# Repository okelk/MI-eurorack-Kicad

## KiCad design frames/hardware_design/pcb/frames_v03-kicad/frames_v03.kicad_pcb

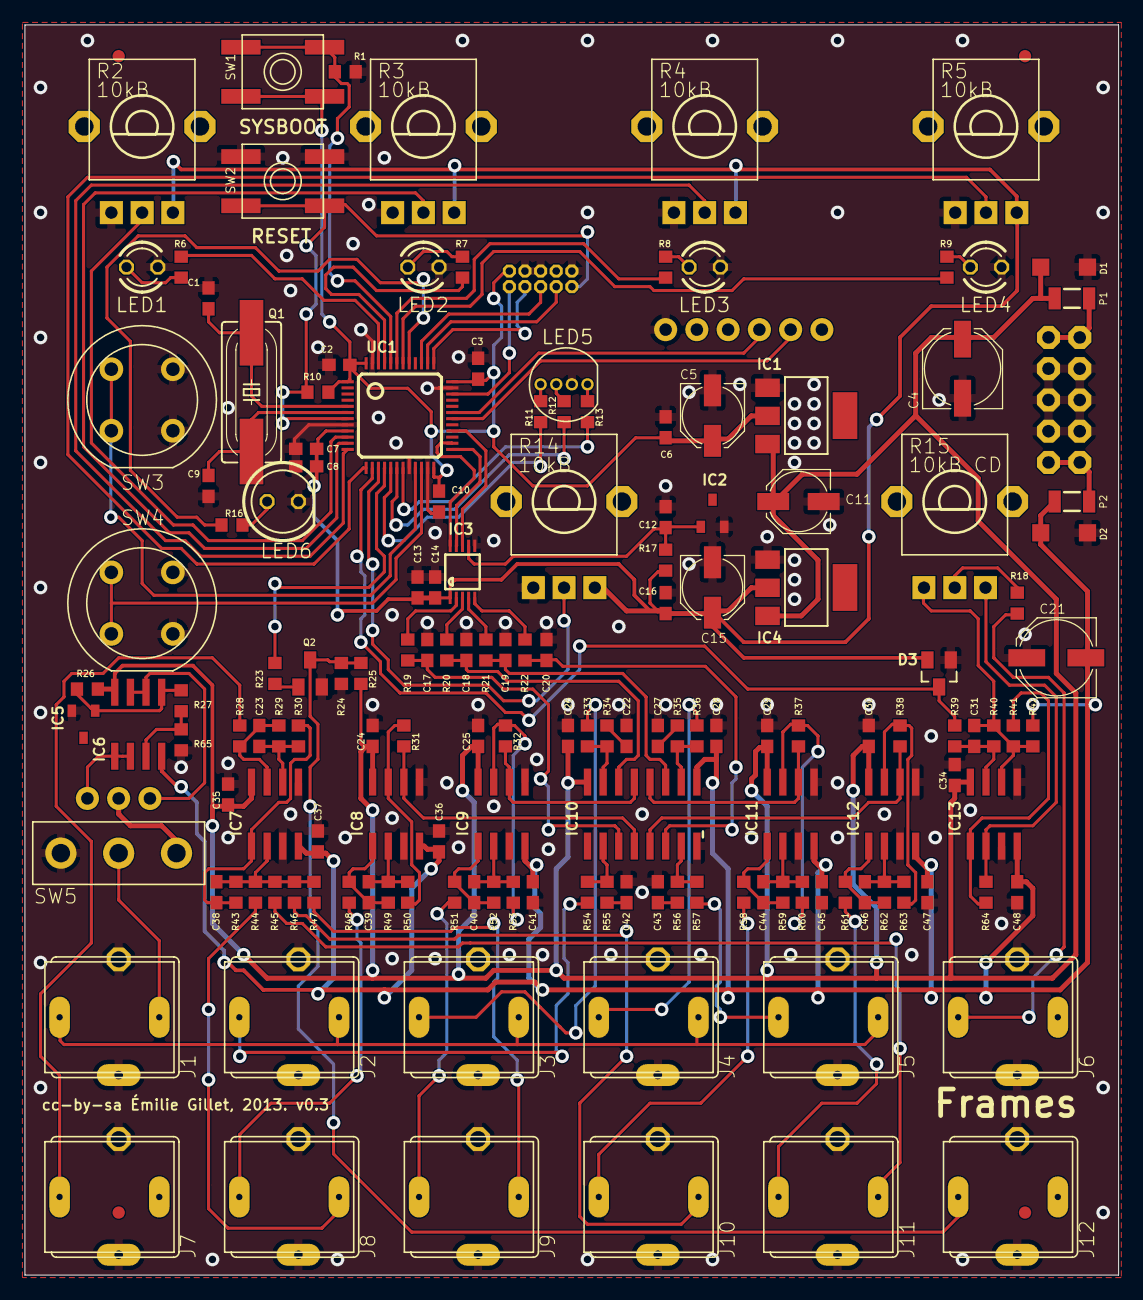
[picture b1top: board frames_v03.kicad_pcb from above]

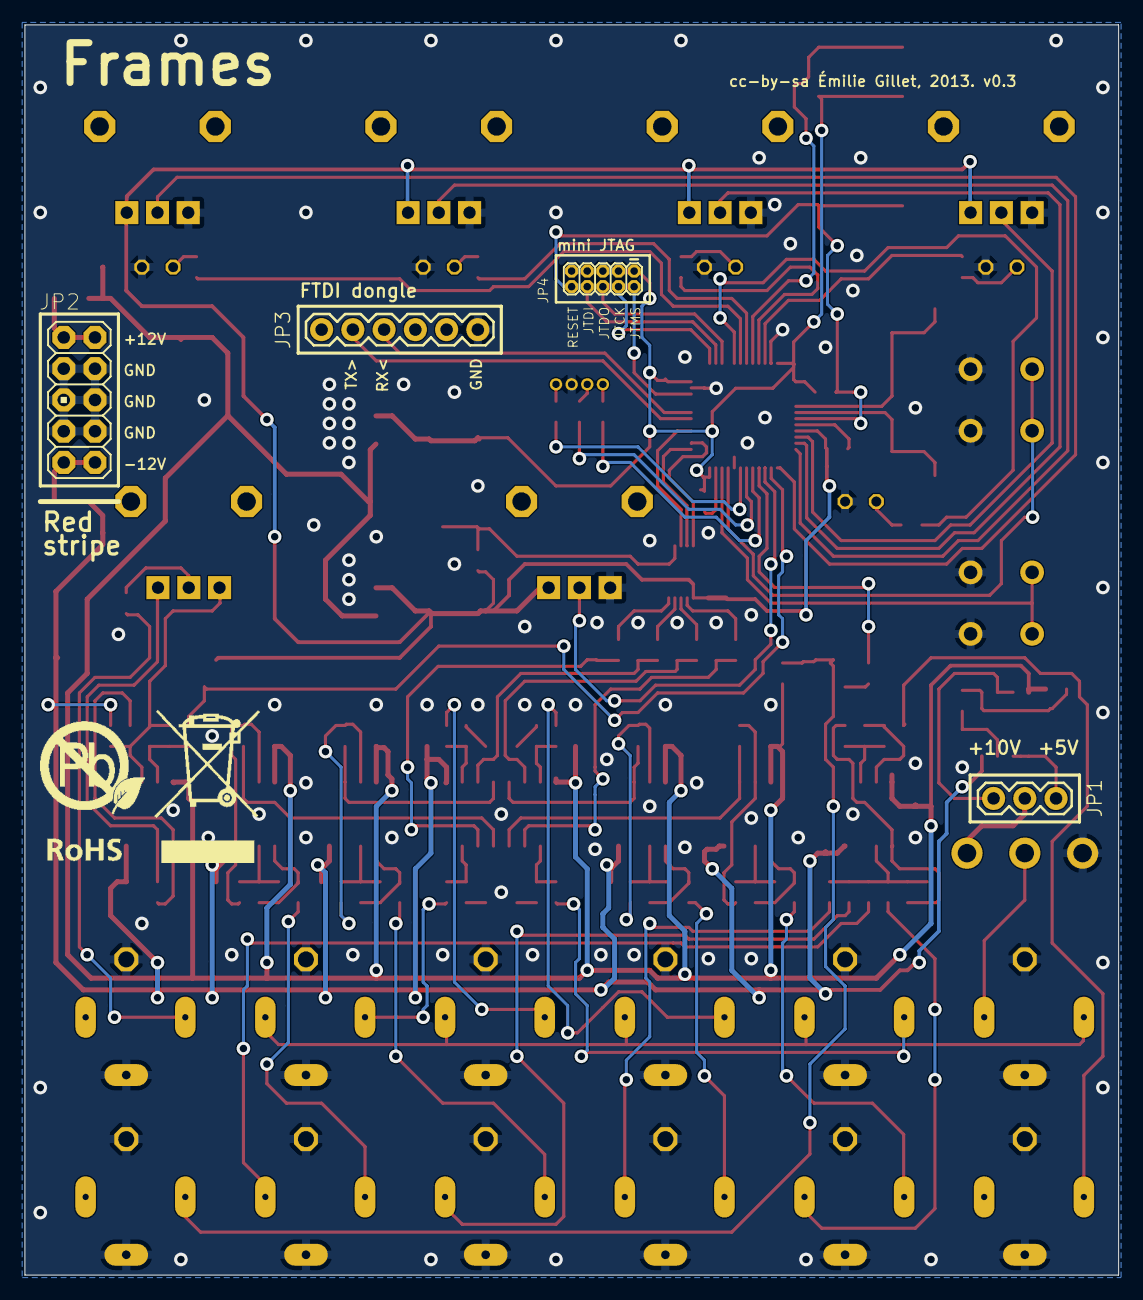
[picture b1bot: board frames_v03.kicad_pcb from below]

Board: 2 copper layers, 88.9 x 101.6 mm, 165 parts (5 on the bottom side), 110 nets.

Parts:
C1, C9, C23, C38, C39, C40, C44, C46: 18p; C0603
C2, C3, C6, C7, C10, C13, C16, C24, C25, C26, C28, C29, C30, C34, C35, C36, C37, C41, C45, C47, C48: 100n; C0603
C4, C21: 47u; PANASONIC_D
C5, C11, C15: 22u; PANASONIC_C
C8, C14: 3.3u; C0603
C12: 470n; C0603
C17, C18, C19, C20: 1u; C0603
C22, C27, C31, C42, C43: 560p; C0603
D1, D2: 1N5819HW; SOD123
D3: BAT54S; SOT23
F1, F2, F3, F4: FIDUCIAL1X2; FIDUCIAL-1X2
IC1, IC4: LM1117-3.3; SOT223
IC2: LM4040B25; DBZ_R-PDSO-G3
IC3: DAC124S085CIMT; MSOP10
IC5: LM4040B10; DBZ_R-PDSO-G3
IC6, IC7, IC8, IC9, IC11, IC12, IC13: TL072D; SO08
IC10: V2164SZ; SOIC16N
J1, J2, J3, J4, J5, J6, J7, J8, J9, J10, J11, J12: PJ301WQP; WQP_PJ_301BM
JP1: 1X03
JP2: M05X2PTH; AVR_ICSP
JP3: 1X06
JP4: M05X2MINIJTAG; 2X5-1.27
LED1, LED2, LED3, LED4: WP710A10GD; LED3MM
LED5: WP154A4SUREQBFZG; LED-TRICOLOR-THROUGHHOLE
LED6: WP7113SGD; LED5MM
P1, P2: PTCSMD; PTC-1206
Q1: 8MHz; HC49UP
Q2: MMBT3904; SOT23-BEC
R1, R10, R23: 10k; R0603
R2, R3, R4, R5, R14: 10kB; ALPS_POT_VERTICAL_PS
R6, R7, R8, R9, R11, R12, R13, R16, R19, R20, R21, R22: 100; R0603
R15: 10kB CD; ALPS_POT_VERTICAL_PS
R17, R34, R35, R55, R56: 510; R0603
R18, R27, R29, R30, R31, R32, R33, R36, R37, R38, R41, R44, R45, R46, R47, R49, R50, R52, R53, R54, R57, R59, R60, R62, R63, R64, R65: 100k; R0603
R24: 3.3k; R0603
R25, R26: 4.7k; R0603
R28, R39, R48, R51, R58, R61: 1.0k; R0603
R40: 33k; R0603
R42: 240k; R0603
R43: 49.9k; R0603
SW1, SW2: EVQ-Q2
SW3, SW4: D6R
SW5: ES_100SP1T6B11M2QEH_SMALL
U$1: EURORACK_TEMPLATE
U$3: ROHS_BIG
UC1: STM32F103CBT6; LQFP48

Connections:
+3V3: C2.1, C3.1, C5.+, C6.1, C10.1, IC1.2, JP4.1, R10.2, SW1.B, SW1.B', UC1.1, UC1.24, UC1.36, UC1.48
+3V3_A: C7.1, C8.1, C13.1, C14.1, C15.+, C16.1, D3.2, IC3.1, IC4.2, R2.P$1, R3.P$1, R4.P$1, R5.P$1, R14.P$1, R17.1, UC1.9
ADD_SWITCH: SW3.A1, SW3.A2, UC1.21
AREF_2.5: C12.1, IC2.1, IC3.7, R17.2
AREF_5: IC6.1, IC6.2, JP1.1
AREF_10: IC6.6, IC6.7, JP1.3
AREF_10_0: IC5.1, IC6.5, R26.2, R27.2
BOOT_FLASH: R1.2, SW1.A, SW1.A', UC1.44
DAC_MOSI: IC3.8, UC1.28
DAC_SCK: IC3.10, UC1.26
DAC_SS: IC3.9, UC1.25
DEL_SWITCH: SW4.A1, SW4.A2, UC1.22
FB_CURRENT: IC10.2, R54.2, R55.2
FB_CURRENT1: IC10.15, R33.2, R34.2
FB_CURRENT2: IC10.10, R35.2, R36.2
FB_CURRENT3: IC10.7, R56.2, R57.2
FRAME_CHANGE: R23.1, UC1.16
GAIN_1: C17.1, IC10.3, R19.2
GAIN_2: C18.1, IC10.14, R20.2
GAIN_3: C19.1, IC10.11, R21.2
GAIN_4: C20.1, IC10.6, R22.2
GATE2_LED: LED3.A, R8.2
GATE3_LED: LED2.A, R7.2
GATE4_LED: LED1.A, R6.2
GND: C1.1, C2.2, C3.2, C4.-, C5.-, C6.2, C7.2, C8.2, C9.1, C10.2, C11.-, C12.2, C13.2, C14.2, C15.-, C16.2, C17.2, C18.2, C19.2, C20.2, C21.+, C22.2, C24.2, C25.2, C26.2, C27.2, C28.1, C29.2, C30.2, C34.2, C35.2, C36.1, C37.1, C41.1, C42.2, C43.2, C45.1, C47.1, C48.1, D1.A, D2.C, D3.1, IC1.1, IC2.2, IC3.6, IC4.1, IC5.2, IC7.3, IC7.5, IC8.3, IC8.5, IC9.3, IC9.5, IC10.8, IC11.3, IC11.5, IC12.3, IC12.5, IC13.3, IC13.5, J1.GND, J1.GND2, J2.GND, J2.GND2, J3.GND, J3.GND2, J4.GND, J4.GND2, J5.GND, J5.GND2, J6.GND, J6.GND2, J7.GND, J7.GND2, J8.GND, J8.GND2, J9.GND, J9.GND2, J10.GND, J10.GND2, J11.GND, J11.GND2, J12.GND, J12.GND2, JP2.3, JP2.4, JP2.5, JP2.6, JP2.7, JP2.8, JP3.1, JP4.3, JP4.5, JP4.9, LED1.K, LED2.K, LED3.K, LED4.K, LED5.GND, LED6.K, Q2.E, R1.1, R2.P$3, R3.P$3, R4.P$3, R5.P$3, R14.P$3, R24.1, R65.1, SW2.A, SW2.A', SW3.B1, SW3.B2, SW4.B1, SW4.B2, SW5.O, UC1.8, UC1.20, UC1.23, UC1.35, UC1.47
IN_1: J2.TIP, R54.1
IN_2: J3.TIP, R33.1
IN_3: J4.TIP, R36.1
IN_4: J5.TIP, R57.1
JTCK: JP4.4, UC1.37
JTDI: JP4.8, UC1.38
JTDO: JP4.6, UC1.39
JTMS: JP4.2, UC1.34
LED_B: R12.1, UC1.18
LED_CH1: R6.1, UC1.46
LED_CH2: R7.1, UC1.45
LED_CH3: R8.1, UC1.43
LED_CH4: R9.1, UC1.42
LED_FRAME: R16.1, UC1.41
LED_G: R11.1, UC1.17
LED_R: R13.1, UC1.19
MODULATION: D3.3, R39.1, UC1.14
unnamed: IC13.2, R15.P$1, R64.2
unnamed: C42.1, R55.1
unnamed: J7.TIP, R28.2
unnamed: IC9.7, R32.2, R53.1
unnamed: R15.P$2, R18.2
unnamed: LED4.A, R9.2
unnamed: C1.2, Q1.2, UC1.5
unnamed: C9.2, Q1.1, UC1.6
unnamed: IC13.1, R41.2, R64.1
unnamed: C27.1, R35.1
unnamed: J6.TIP, R18.1
unnamed: IC8.6, IC10.4, R31.1
unnamed: C31.2, IC13.7, R39.2, R40.1
unnamed: C31.1, IC13.6, R15.P$3, R40.2, R41.1, R42.1
unnamed: C39.1, IC8.2, R49.1, R50.2
unnamed: C39.2, IC8.1, R48.1, R49.2
unnamed: C23.2, IC7.7, R28.1, R29.2
unnamed: C22.1, R34.1
unnamed: C38.1, IC7.2, R43.1, R44.2, R45.2, R46.2, R47.2
unnamed: IC9.6, IC10.13, R32.1
unnamed: C23.1, IC7.6, R29.1, R30.2
unnamed: C40.1, IC9.2, R52.1, R53.2
unnamed: C40.2, IC9.1, R51.1, R52.2
unnamed: IC10.12, IC11.6, R37.1
unnamed: LED6.A, R16.2
unnamed: C44.1, IC11.2, R59.1, R60.2
unnamed: C44.2, IC11.1, R58.1, R59.2
unnamed: C43.1, R56.1
unnamed: C38.2, IC7.1, R30.1, R43.2
unnamed: IC10.5, IC12.6, R38.1
unnamed: IC6.3, R27.1, R65.2
unnamed: C46.1, IC12.2, R62.1, R63.2
unnamed: C46.2, IC12.1, R61.1, R62.2
unnamed: J1.SW, SW5.P
unnamed: LED5.RED, R13.2
unnamed: LED5.BLU, R12.2
unnamed: LED5.GRN, R11.2
unnamed: IC3.2, R19.1
unnamed: J8.TIP, R48.2
unnamed: IC3.3, R20.1
unnamed: JP1.2, SW5.S
unnamed: IC3.4, R21.1
unnamed: J12.TIP, Q2.C, R24.2, R25.1
unnamed: IC3.5, R22.1
unnamed: Q2.B, R23.2
unnamed: IC12.7, R38.2, R63.1
unnamed: J9.TIP, R51.2
unnamed: J11.TIP, R61.2
unnamed: J10.TIP, R58.2
unnamed: JP2.1, JP2.2, P1.2
unnamed: JP2.9, JP2.10, P2.2
PAN: J1.TIP, J2.SW, J3.SW, J4.SW, J5.SW
POT_CH1: R2.P$2, UC1.10
POT_CH2: R3.P$2, UC1.11
POT_CH3: R4.P$2, UC1.12
POT_CH4: R5.P$2, UC1.13
POT_FRAME: R14.P$2, UC1.15
RESET: JP4.10, R10.1, SW2.B, SW2.B', UC1.7
RX: JP3.4, UC1.31
TX: JP3.5, UC1.30
VCA0_1: IC8.7, R31.2, R50.1
VCA0_3: IC11.7, R37.2, R60.1
VCA_1: J8.SW, R44.1
VCA_2: J9.SW, R47.1
VCA_3: J10.SW, R46.1
VCA_4: J11.SW, R45.1
VCC: C4.+, C11.+, C24.1, C25.1, C26.1, C29.1, C30.1, C34.1, C35.1, D1.C, IC1.3, IC4.3, IC6.8, IC7.8, IC8.8, IC9.8, IC10.16, IC11.8, IC12.8, IC13.8, P1.1, R25.2, R26.1
VEE: C21.-, C28.2, C36.2, C37.2, C41.2, C45.2, C47.2, C48.2, D2.A, IC6.4, IC7.4, IC8.4, IC9.4, IC10.9, IC11.4, IC12.4, IC13.4, P2.1, R42.2

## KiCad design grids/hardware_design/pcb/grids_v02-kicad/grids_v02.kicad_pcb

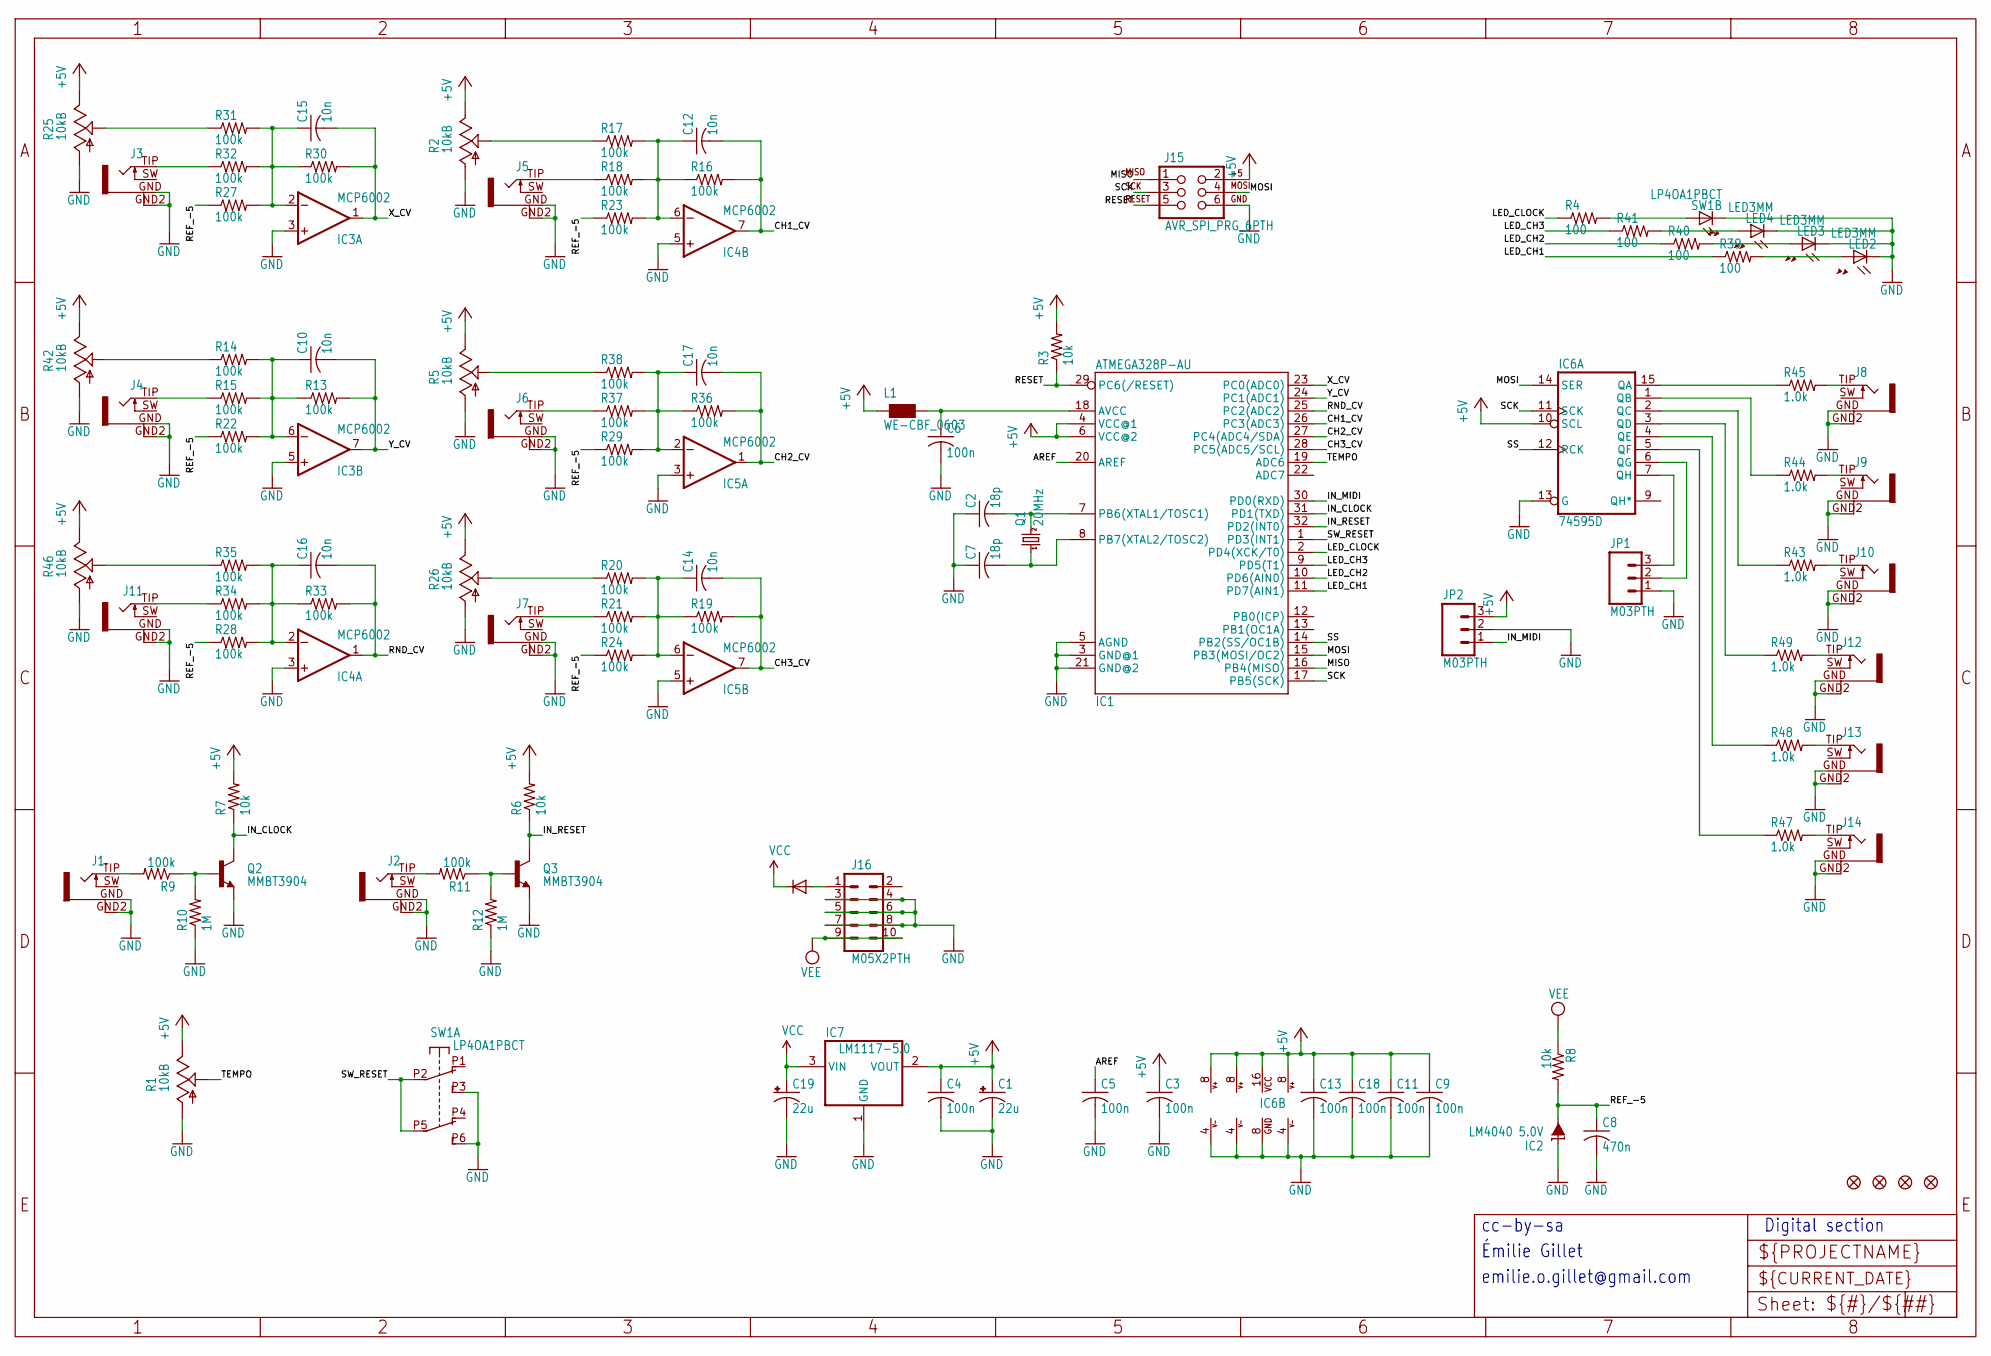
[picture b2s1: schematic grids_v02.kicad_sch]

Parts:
C1, C19: 22u; PANASONIC_C
C2, C7: 18p; C0603
C3, C4, C5, C6, C9, C11, C13, C18: 100n; C0603
C8: 470n; C0603
C10, C12, C14, C15, C16, C17: 10n; C0603
D1: 1N5819HW; SOD123
F1, F2, F3, F4: FIDUCIAL1X2; FIDUCIAL-1X2
IC1: ATMEGA328P-AU; TQFP32-08
IC2: LM4040 5.0V; DBZ_R-PDSO-G3
IC3, IC4, IC5: MCP6002; SO08
IC6: 74595D; SO16
IC7: LM1117-5.0; SOT223
J1, J2, J3, J4, J5, J6, J7, J8, J9, J10, J11, J12, J13, J14: PJ301WQP; WQP_PJ_301BM
J15: AVR_SPI_PRG_6PTH; 2X3
J16: M05X2PTH; AVR_ICSP
JP1, JP2: M03PTH; 1X03
L1: WE-CBF_0603; 0603
LED2, LED3, LED4: LED3MM
Q1: 20MHz; HC49UP
Q2, Q3: MMBT3904; SOT23-BEC
R1, R2, R5, R25, R26, R46: 10kB; ALPS_POT_VERTICAL_PS
R3, R6, R7, R8: 10k; R0603
R4, R39, R40, R41: 100; R0603
R9, R11, R13, R14, R15, R16, R17, R18, R19, R20, R21, R22, R23, R24, R27, R28, R29, R30, R31, R32, R33, R34, R35, R36, R37, R38: 100k; R0603
R10, R12: 1M; R0603
R42: 10kB; ALPS_POT_VERTICAL_PS4
R43, R44, R45, R47, R48, R49: 1.0k; R0603
SW1: LP4OA1PBCT

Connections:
+5V: C1.+, C3.1, C4.1, C9.1, C11.1, C13.1, C18.1, IC1.4 (VCC@1), IC1.6 (VCC@2), IC3.8 (V+), IC4.8 (V+), IC5.8 (V+), IC6.10 (SCL), IC6.16 (VCC), IC7.2 (VOUT), J15.2, JP2.3, L1.1, R1.P$1 (E), R2.P$1 (E), R3.2, R5.P$1 (E), R6.2, R7.2, R25.P$1 (E), R26.P$1 (E), R42.P$1 (E), R46.P$1 (E)
AREF: C5.1, IC1.20 (AREF)
CH1_CV: C12.2, IC1.26 (PC3(ADC3)), IC4.7 (OUT), R16.2
CH2_CV: C17.2, IC1.27 (PC4(ADC4/SDA)), IC5.1 (OUT), R36.2
CH3_CV: C14.2, IC1.28 (PC5(ADC5/SCL)), IC5.7 (OUT), R19.2
CLOCK_OUT: IC6.6 (QG), JP1.2
GATE1_IN: J1.TIP (2), R9.2
GATE1_LED: R4.2, SW1.L1
GATE2_IN: J2.TIP (2), R11.2
GATE2_LED: LED4.A, R41.2
GATE3_LED: LED3.A, R40.2
GATE4_LED: LED2.A, R39.2
GND: C1.-, C2.1, C3.2, C4.2, C5.2, C6.2, C7.1, C8.2, C9.2, C11.2, C13.2, C18.2, C19.-, IC1.3 (GND@1), IC1.5 (AGND), IC1.21 (GND@2), IC2.1 (C), IC3.3 (+IN), IC3.4 (V-), IC3.5 (+IN), IC4.3 (+IN), IC4.4 (V-), IC4.5 (+IN), IC5.3 (+IN), IC5.4 (V-), IC5.5 (+IN), IC6.8 (GND), IC6.13 (G), IC7.1 (GND), J1.GND (1), J1.GND2 (4), J2.GND (1), J2.GND2 (4), J3.GND (1), J3.GND2 (4), J4.GND (1), J4.GND2 (4), J5.GND (1), J5.GND2 (4), J6.GND (1), J6.GND2 (4), J7.GND (1), J7.GND2 (4), J8.GND (1), J8.GND2 (4), J9.GND (1), J9.GND2 (4), J10.GND (1), J10.GND2 (4), J11.GND (1), J11.GND2 (4), J12.GND (1), J12.GND2 (4), J13.GND (1), J13.GND2 (4), J14.GND (1), J14.GND2 (4), J15.6, J16.3, J16.4, J16.5, J16.6, J16.7, J16.8, JP1.1, JP2.2, LED2.K (C), LED3.K (C), LED4.K (C), Q2.E, Q3.E, R1.P$3 (A), R2.P$3 (A), R5.P$3 (A), R10.1, R12.1, R25.P$3 (A), R26.P$3 (A), R42.P$3 (A), R46.P$3 (A), SW1.L2, SW1.P3 (A3), SW1.P6 (B3)
IN_CLOCK: IC1.31 (PD1(TXD)), Q2.C, R7.1
IN_MIDI: IC1.30 (PD0(RXD)), JP2.1
IN_RESET: IC1.32 (PD2(INT0)), Q3.C, R6.1
LED_CH1: IC1.11 (PD7(AIN1)), R39.1
LED_CH2: IC1.10 (PD6(AIN0)), R40.1
LED_CH3: IC1.9 (PD5(T1)), R41.1
LED_CLOCK: IC1.2 (PD4(XCK/T0)), R4.1
MISO: IC1.16 (PB4(MISO)), J15.1
MOSI: IC1.15 (PB3(MOSI/OC2)), IC6.14 (SER), J15.4
unnamed: Q2.B, R9.1, R10.2
unnamed: Q3.B, R11.1, R12.2
unnamed: D1.A, J16.1
unnamed: J14.TIP (2), R47.2
unnamed: J13.TIP (2), R48.2
unnamed: J12.TIP (2), R49.2
unnamed: R25.P$2 (S), R31.1
unnamed: J3.TIP (2), R32.1
unnamed: C10.1, IC3.6 (-IN), R13.1, R14.2, R15.2, R22.2
unnamed: R14.1, R42.P$2 (S)
unnamed: J4.TIP (2), R15.1
unnamed: C16.1, IC4.2 (-IN), R28.2, R33.1, R34.2, R35.2
unnamed: R35.1, R46.P$2 (S)
unnamed: J11.TIP (2), R34.1
unnamed: C12.1, IC4.6 (-IN), R16.1, R17.2, R18.2, R23.2
unnamed: R2.P$2 (S), R17.1
unnamed: J5.TIP (2), R18.1
unnamed: C17.1, IC5.2 (-IN), R29.2, R36.1, R37.2, R38.2
unnamed: R5.P$2 (S), R38.1
unnamed: J6.TIP (2), R37.1
unnamed: C14.1, IC5.6 (-IN), R19.1, R20.2, R21.2, R24.2
unnamed: R20.1, R26.P$2 (S)
unnamed: J7.TIP (2), R21.1
unnamed: IC6.15 (QA), R45.1
unnamed: IC6.1 (QB), R44.1
unnamed: C15.1, IC3.2 (-IN), R27.2, R30.1, R31.2, R32.2
unnamed: IC6.2 (QC), R43.1
unnamed: IC6.3 (QD), R49.1
unnamed: IC6.4 (QE), R48.1
unnamed: IC6.5 (QF), R47.1
unnamed: J8.TIP (2), R45.2
unnamed: J9.TIP (2), R44.2
unnamed: J10.TIP (2), R43.2
unnamed: C6.1, IC1.18 (AVCC), L1.2
unnamed: C7.2, IC1.8 (PB7(XTAL2/TOSC2)), Q1.1
unnamed: C2.2, IC1.7 (PB6(XTAL1/TOSC1)), Q1.2
RANDOM_GATE: IC6.7 (QH), JP1.3
REF_-5: C8.1, IC2.2 (A), R8.2, R22.1, R23.1, R24.1, R27.1, R28.1, R29.1
RESET: IC1.29 (PC6(/RESET)), J15.5, R3.1
RND_CV: C16.2, IC1.25 (PC2(ADC2)), IC4.1 (OUT), R33.2
SCK: IC1.17 (PB5(SCK)), IC6.11 (SCK), J15.3
SS: IC1.14 (PB2(SS/OC1B)), IC6.12 (RCK)
SW_RESET: IC1.1 (PD3(INT1)), SW1.P2 (A2), SW1.P5 (B2)
TEMPO: IC1.19 (ADC6), R1.P$2 (S)
VCC: C19.+, D1.C, IC7.3 (VIN)
VEE: J16.9, J16.10, R8.1
X_CV: C15.2, IC1.23 (PC0(ADC0)), IC3.1 (OUT), R30.2
Y_CV: C10.2, IC1.24 (PC1(ADC1)), IC3.7 (OUT), R13.2

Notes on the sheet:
Digital section
Émilie Gillet
cc-by-sa
emilie.o.gillet@gmail.com

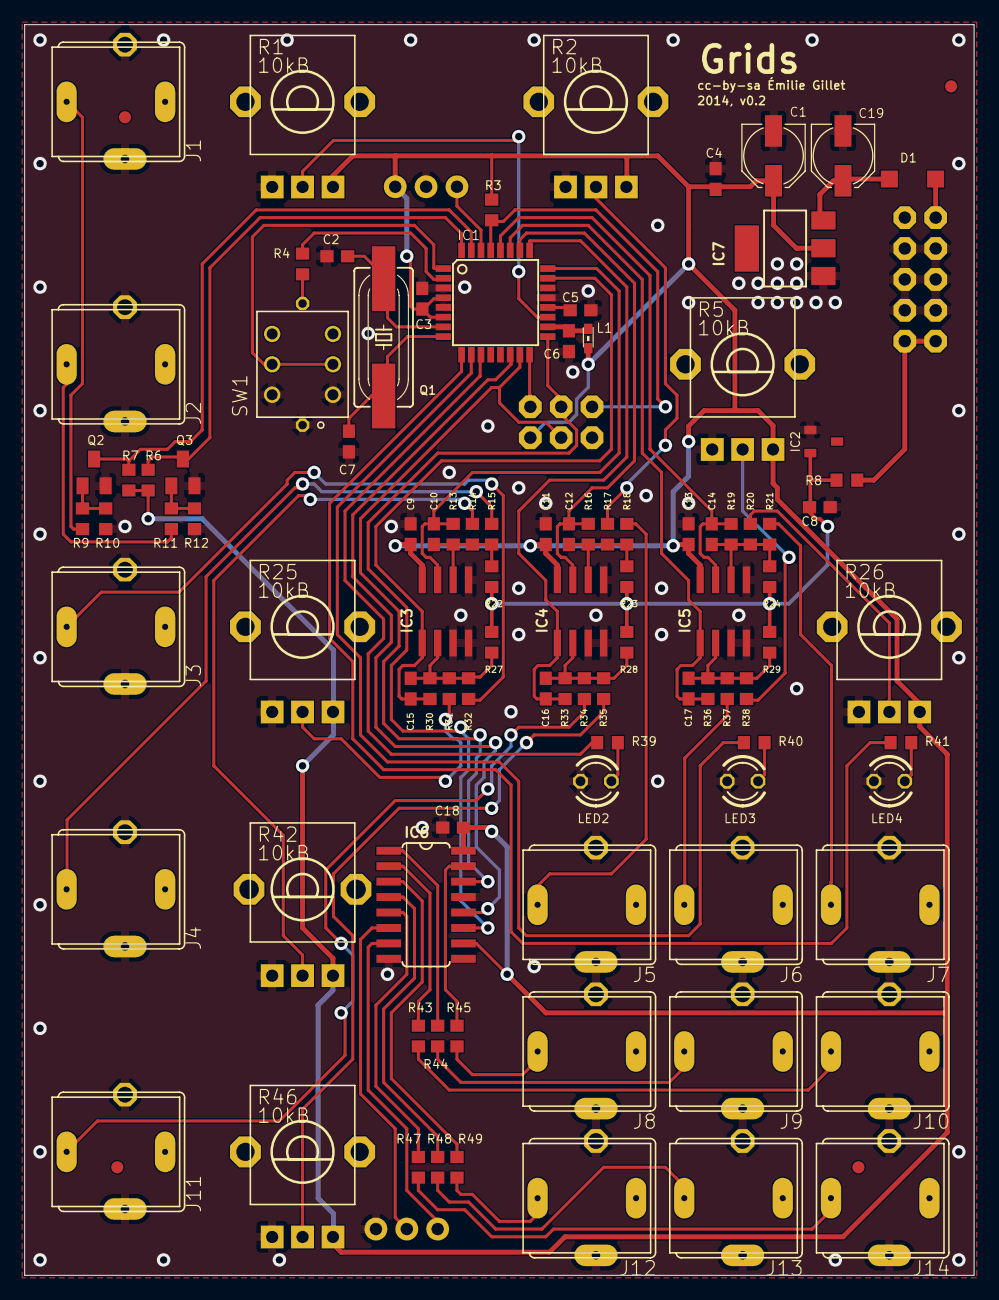
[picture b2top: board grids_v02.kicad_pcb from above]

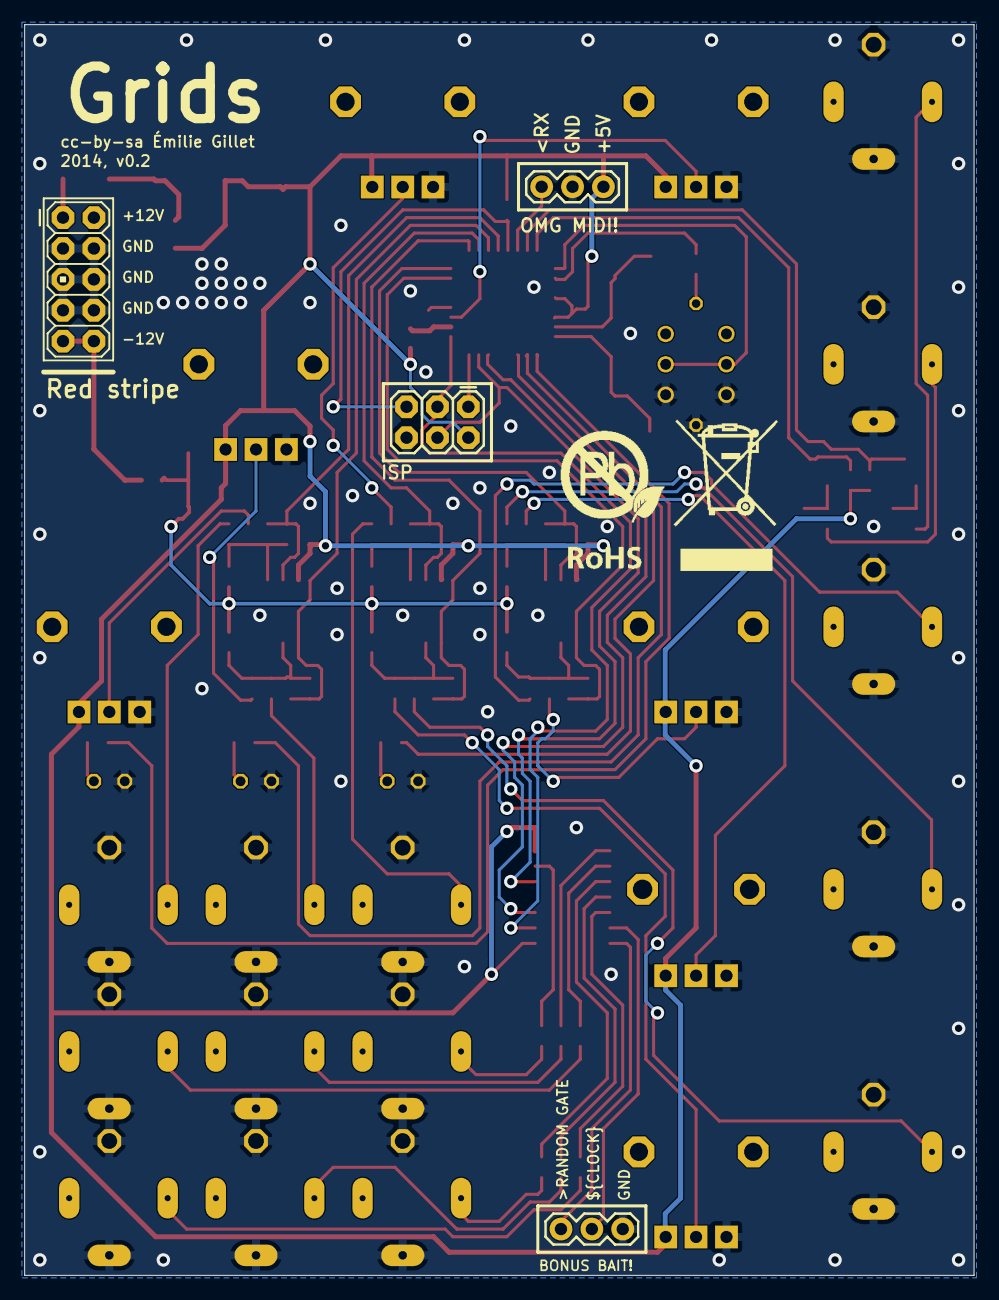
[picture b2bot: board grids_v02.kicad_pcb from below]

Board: 2 copper layers, 78.1 x 102.9 mm, 108 parts (5 on the bottom side), 70 nets.

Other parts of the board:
U$1: EURORACK_TEMPLATE
U$2: ROHS_BIG

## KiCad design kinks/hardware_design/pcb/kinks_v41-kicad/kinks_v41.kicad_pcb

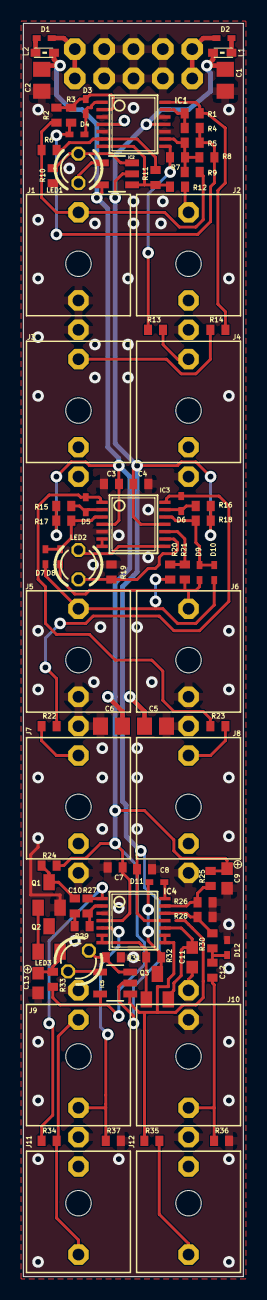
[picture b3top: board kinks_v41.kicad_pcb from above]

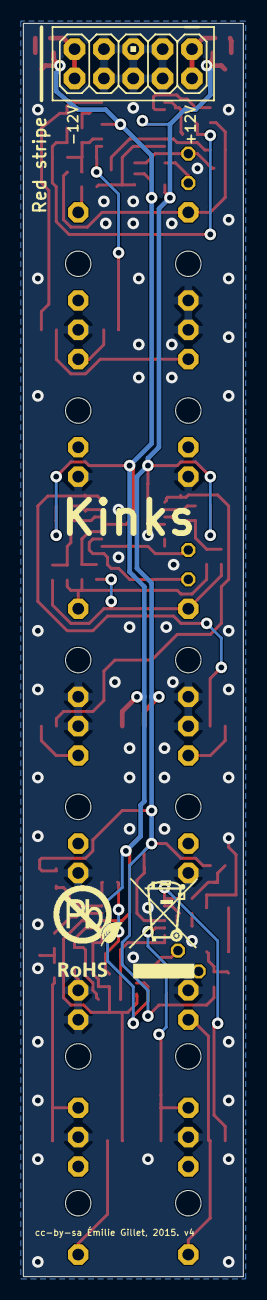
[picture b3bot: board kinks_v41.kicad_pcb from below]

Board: 2 copper layers, 19.0 x 108.4 mm, 89 parts (2 on the bottom side), 56 nets.

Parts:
C1, C2, C5, C6: 22u; C0805
C3, C4, C7, C8, C10: 100n; C0402
C9, C13: 4.7u; C0603
C11: 10n; C0603
C12: 100p; C0402
D1, D2: PMEG2010AEB; SOD523
D3, D4, D5, D6, D7, D8, D9, D10, D11, D12: 1N4148; SOD523
IC1, IC3: TL074PW; TSSOP14
IC2, IC5: LM321MF; SOT23-5
IC4: OPA4171; TSSOP14
J1, J2, J3, J4, J5, J6, J7, J8, J9, J10, J11, J12: PJ301_THONKICONN6; WQP_PJ_301M6
JP1: M05X2PTH; AVR_ICSP
L1, L2: 0603
LED1, LED2, LED3: WP937EGW; LED3MM
Q1, Q2: MMBT3904; SOT23-BEC
Q3: MMBFJ309; SOT23
R1, R2, R6, R7, R9, R11: 200k; R0402
R3, R4, R5, R8, R28, R29, R36: 100k; R0402
R10, R19, R31: 1.0k; R0402
R12, R13, R14, R22, R23, R34, R35: 180; R0402
R15, R16, R17, R18: 220k; R0402
R20, R21, R25, R32, R37: 1.0M; R0402
R24: 4.7k; R0402
R26, R30: 10k; R0402
R27: 1.5M; R0402
R33: 470k; R0402
U$2: ROHS

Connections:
A: D7.C, D10.A, J5.P3, R20.2
B: D8.C, D9.A, J6.P3, R21.2
GND: C1.1, C2.2, C3.2, C4.1, C5.1, C6.2, C7.2, C8.1, C9.2, C11.2, C13.2, D12.A, IC1.3, IC1.5, IC1.10, IC1.12, IC3.5, IC4.3, J1.P1, J1.P2, J2.P1, J3.P1, J4.P1, J5.P1, J5.P2, J6.P1, J6.P2, J7.P1, J8.P1, J9.P1, J10.P1, J10.P2, J11.P1, J12.P1, JP1.3, JP1.4, JP1.5, JP1.6, JP1.7, JP1.8, Q1.E, R10.2, R19.2, R26.1, R28.1, R31.2, R36.1, R37.2
unnamed: D9.C, D10.C, IC3.12, R18.1
unnamed: D6.A, IC3.14, R22.2
unnamed: IC4.8, IC4.9, IC5.1, R35.2
unnamed: D6.C, IC3.13, R16.1
unnamed: D7.A, D8.A, IC3.3, R17.1
unnamed: D1.A, JP1.1, JP1.2
unnamed: IC3.6, IC3.7
unnamed: Q1.B, Q2.B
unnamed: IC2.3, LED1.K, R10.1
unnamed: D5.C, IC3.1, R23.2
unnamed: IC2.4, LED1.A
unnamed: C13.1, Q2.E, R33.2
unnamed: C10.2, R29.2
unnamed: IC3.8, LED2.K
unnamed: D5.A, IC3.2, R15.1
unnamed: IC4.2, R27.2, R29.1
unnamed: J8.P3, R23.1
unnamed: IC3.10, R20.1, R21.1
unnamed: IC5.3, LED3.A, R31.1
unnamed: D2.C, JP1.9, JP1.10
unnamed: IC1.6, R6.1, R11.2
unnamed: D1.C, L2.2
unnamed: IC1.7, IC2.1, R11.1, R12.2
unnamed: J2.P3, R12.1
unnamed: D3.C, IC1.2, R2.1, R3.2
unnamed: D3.A, D4.C, IC1.1
unnamed: IC1.14, R1.1, R14.2
unnamed: IC1.13, R1.2, R4.1
unnamed: IC3.9, LED2.A, R19.1
unnamed: IC5.4, LED3.K
unnamed: C10.1, Q1.C, R24.1
unnamed: J3.P3, R14.1
unnamed: IC1.9, R5.1, R7.2, R8.1, R9.1
unnamed: J4.P3, R13.1
unnamed: IC1.8, R7.1, R13.2
unnamed: IC4.1, R27.1, R34.2
unnamed: J9.P2, J11.P3, R34.1
unnamed: J1.P3, R2.2, R6.2, R9.2
unnamed: D4.A, R3.1, R4.2, R5.2, R8.2
unnamed: IC4.5, J9.P3, R37.1
unnamed: IC4.6, IC4.7, Q3.1, R32.2
unnamed: D11.A, Q3.3, R32.1
unnamed: D11.C, IC4.14
unnamed: D2.A, L1.2
unnamed: C11.1, IC4.10, Q3.2
unnamed: IC4.12, R28.2, R30.2
unnamed: J7.P3, R22.1
unnamed: J12.P3, R35.1
unnamed: C12.1, J10.P3, R36.2
unnamed: IC4.13, R25.1, R26.2
unnamed: C12.2, D12.C, R30.1
VCC: C2.1, C3.1, C6.1, C7.1, C9.1, IC1.4, IC2.5, IC3.4, IC4.4, IC5.5, L2.1, R15.2, R17.2, R24.2, R25.2, R33.1
VEE: C1.2, C4.2, C5.2, C8.2, IC1.11, IC2.2, IC3.11, IC4.11, IC5.2, L1.1, R16.2, R18.2

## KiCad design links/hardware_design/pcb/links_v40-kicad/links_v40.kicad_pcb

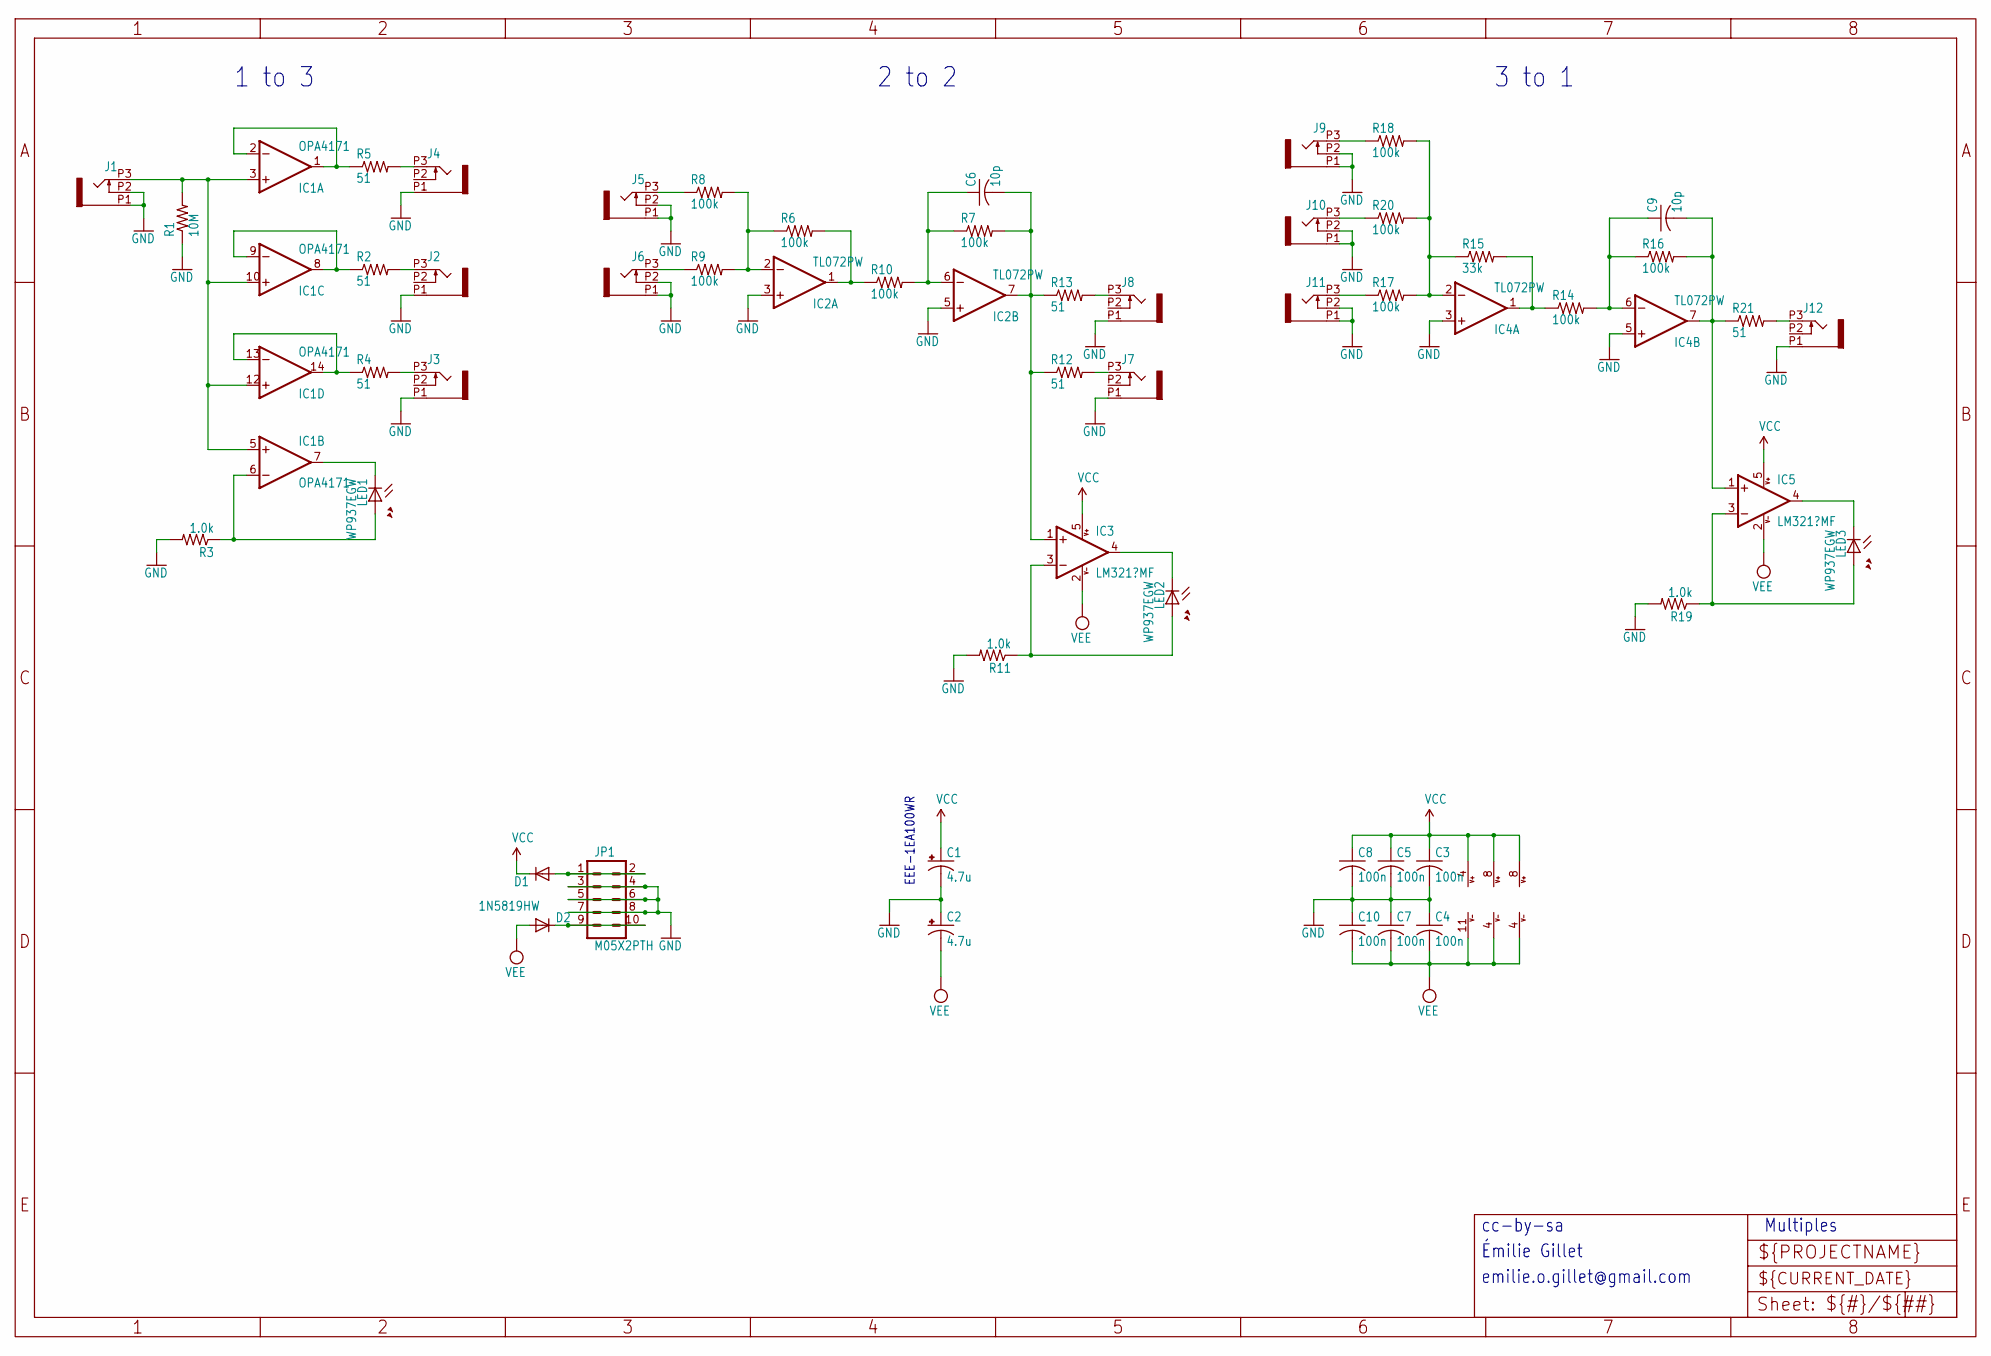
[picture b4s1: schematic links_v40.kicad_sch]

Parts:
C1, C2: 4.7u; PANASONIC_A
C3, C4, C5, C7, C8, C10: 100n; C0603
C6, C9: 10p; C0603
D1, D2: 1N5819HW; SOD123
IC1: OPA4171; TSSOP14
IC2, IC4: TL072PW; TSSOP8
IC3, IC5: LM321?MF; SOT23-5
J1, J2, J3, J4, J5, J6, J7, J8, J9, J10, J11, J12: PJ301_THONKICONN6; WQP_PJ_301M6
JP1: M05X2PTH; AVR_ICSP
LED1, LED2, LED3: WP937EGW; LED3MM
R1: 10M; R0603
R2, R4, R5, R12, R13, R21: 51; R0603
R3, R11, R19: 1.0k; R0603
R6, R7, R8, R9, R10, R14, R16, R17, R18, R20: 100k; R0603
R15: 33k; R0603

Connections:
GND: C1.-, C2.+, C3.2, C4.1, C5.2, C7.1, C8.2, C10.1, IC2.3 (+IN), IC2.5 (+IN), IC4.3 (+IN), IC4.5 (+IN), J1.P1 (1), J1.P2 (2), J2.P1 (1), J3.P1 (1), J4.P1 (1), J5.P1 (1), J5.P2 (2), J6.P1 (1), J6.P2 (2), J7.P1 (1), J8.P1 (1), J9.P1 (1), J9.P2 (2), J10.P1 (1), J10.P2 (2), J11.P1 (1), J11.P2 (2), J12.P1 (1), JP1.3, JP1.4, JP1.5, JP1.6, JP1.7, JP1.8, R1.1, R3.2, R11.2, R19.2
unnamed: IC2.1 (OUT), R6.2, R10.1
unnamed: J11.P3 (3), R17.1
unnamed: IC1.1 (OUT), IC1.2 (-IN), R5.1
unnamed: IC1.8 (OUT), IC1.9 (-IN), R2.1
unnamed: IC1.13 (-IN), IC1.14 (OUT), R4.1
unnamed: D1.A, JP1.1, JP1.2
unnamed: IC1.3 (+IN), IC1.5 (+IN), IC1.10 (+IN), IC1.12 (+IN), J1.P3 (3), R1.2
unnamed: IC1.7 (OUT), LED1.K (C)
unnamed: J10.P3 (3), R20.1
unnamed: J6.P3 (3), R9.1
unnamed: J4.P3 (3), R5.2
unnamed: J2.P3 (3), R2.2
unnamed: J3.P3 (3), R4.2
unnamed: IC3.4 (OUT), LED2.K (C)
unnamed: J5.P3 (3), R8.1
unnamed: J7.P3 (3), R12.2
unnamed: J8.P3 (3), R13.2
unnamed: C9.2, IC4.7 (OUT), IC5.1 (+IN), R16.2, R21.1
unnamed: IC5.3 (-IN), LED3.A, R19.1
unnamed: D2.C, JP1.9, JP1.10
unnamed: IC1.6 (-IN), LED1.A, R3.1
unnamed: J9.P3 (3), R18.1
unnamed: J12.P3 (3), R21.2
unnamed: IC4.2 (-IN), R15.1, R17.2, R18.2, R20.2
unnamed: IC4.1 (OUT), R14.1, R15.2
unnamed: C6.2, IC2.7 (OUT), IC3.1 (+IN), R7.2, R12.1, R13.1
unnamed: C9.1, IC4.6 (-IN), R14.2, R16.1
unnamed: IC3.3 (-IN), LED2.A, R11.1
unnamed: IC5.4 (OUT), LED3.K (C)
unnamed: IC2.2 (-IN), R6.1, R8.2, R9.2
unnamed: C6.1, IC2.6 (-IN), R7.1, R10.2
VCC: C1.+, C3.1, C5.1, C8.1, D1.C, IC1.4 (V+), IC2.8 (V+), IC3.5 (V+), IC4.8 (V+), IC5.5 (V+)
VEE: C2.-, C4.2, C7.2, C10.2, D2.A, IC1.11 (V-), IC2.4 (V-), IC3.2 (V-), IC4.4 (V-), IC5.2 (V-)

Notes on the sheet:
Émilie Gillet
2 to 2
EEE-1EA100WR
3 to 1
Multiples
cc-by-sa
1 to 3
emilie.o.gillet@gmail.com

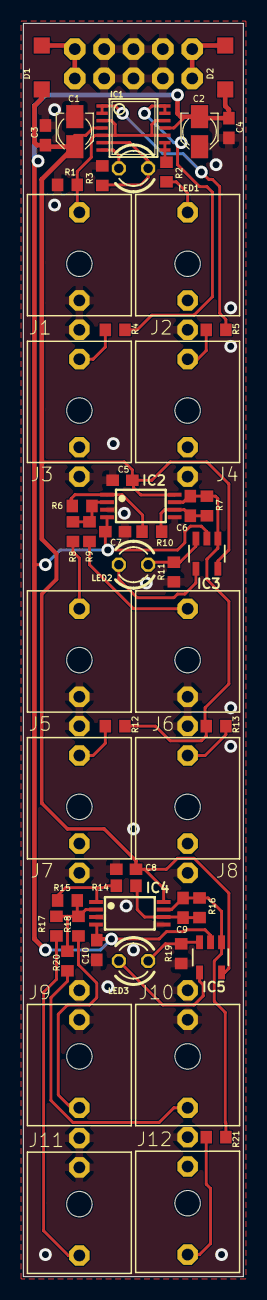
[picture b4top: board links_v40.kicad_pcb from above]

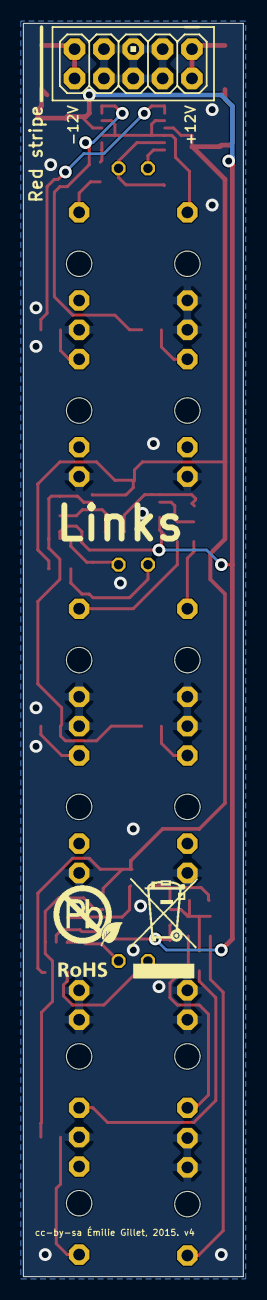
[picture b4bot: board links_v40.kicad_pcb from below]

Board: 2 copper layers, 19.0 x 108.4 mm, 55 parts (2 on the bottom side), 34 nets.

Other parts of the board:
U$2: ROHS

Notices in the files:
frames/hardware_design/pcb/frames_v03-kicad/frames_v03.kicad_pcb:
cc-by-sa Émilie Gillet, 2013. v0.3
kinks/hardware_design/pcb/kinks_v41-kicad/kinks_v41.kicad_pcb:
cc-by-sa Émilie Gillet, 2015. v4
peaks/hardware_design/pcb/peaks_v30-kicad/peaks_v30.kicad_pcb:
cc-by-sa Émilie Gillet, 2015. v3
